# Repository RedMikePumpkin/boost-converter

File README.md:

# boost-converter
Files for my science inquiry project on boost converters

## I am currently locating the files, and they will be uploaded before 22.02.2020

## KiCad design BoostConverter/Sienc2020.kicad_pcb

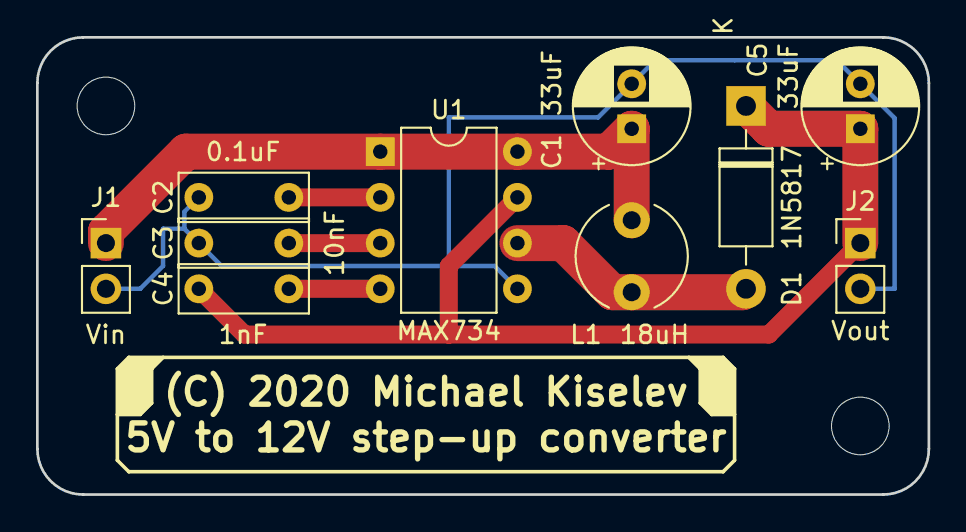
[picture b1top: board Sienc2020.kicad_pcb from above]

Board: 2 copper layers, 49.5 x 25.4 mm, 12 parts (0 on the bottom side), 7 nets.

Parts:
C1, C5: 33uF; CP_Radial_D6.3mm_P2.50mm
C2: 0.1uF; C_Rect_L7.0mm_W2.5mm_P5.00mm
C3: 10nF; C_Rect_L7.0mm_W2.5mm_P5.00mm
C4: 1nF; C_Rect_L7.0mm_W2.5mm_P5.00mm
D1: 1N5817; D_DO-41_SOD81_P10.16mm_Horizontal
H1, H2: MountingHole; MountingHole_3.2mm_M3
J1: Vin; PinHeader_1x02_P2.54mm_Vertical
J2: Vout; PinHeader_1x02_P2.54mm_Vertical
L1: 18uH; L_Radial_D6.0mm_P4.00mm
U1: MAX734; DIP-8_W7.62mm

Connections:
GND: C1.2, C2.2, C3.2, C5.2, J1.2, J2.2, U1.5
unnamed: C1.1, J1.1, L1.1, U1.1, U1.8
unnamed: C2.1, U1.2
unnamed: C3.1, U1.3
unnamed: C4.1, U1.4
unnamed: C4.2, C5.1, D1.1, J2.1, U1.7
unnamed: D1.2, L1.2, U1.6

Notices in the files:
BoostConverter/Sienc2020.kicad_pcb:
(C) 2020 Michael Kiselev
